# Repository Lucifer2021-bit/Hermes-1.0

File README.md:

# Hermes-1.0
PCB para aplicación de comedor para mascotas

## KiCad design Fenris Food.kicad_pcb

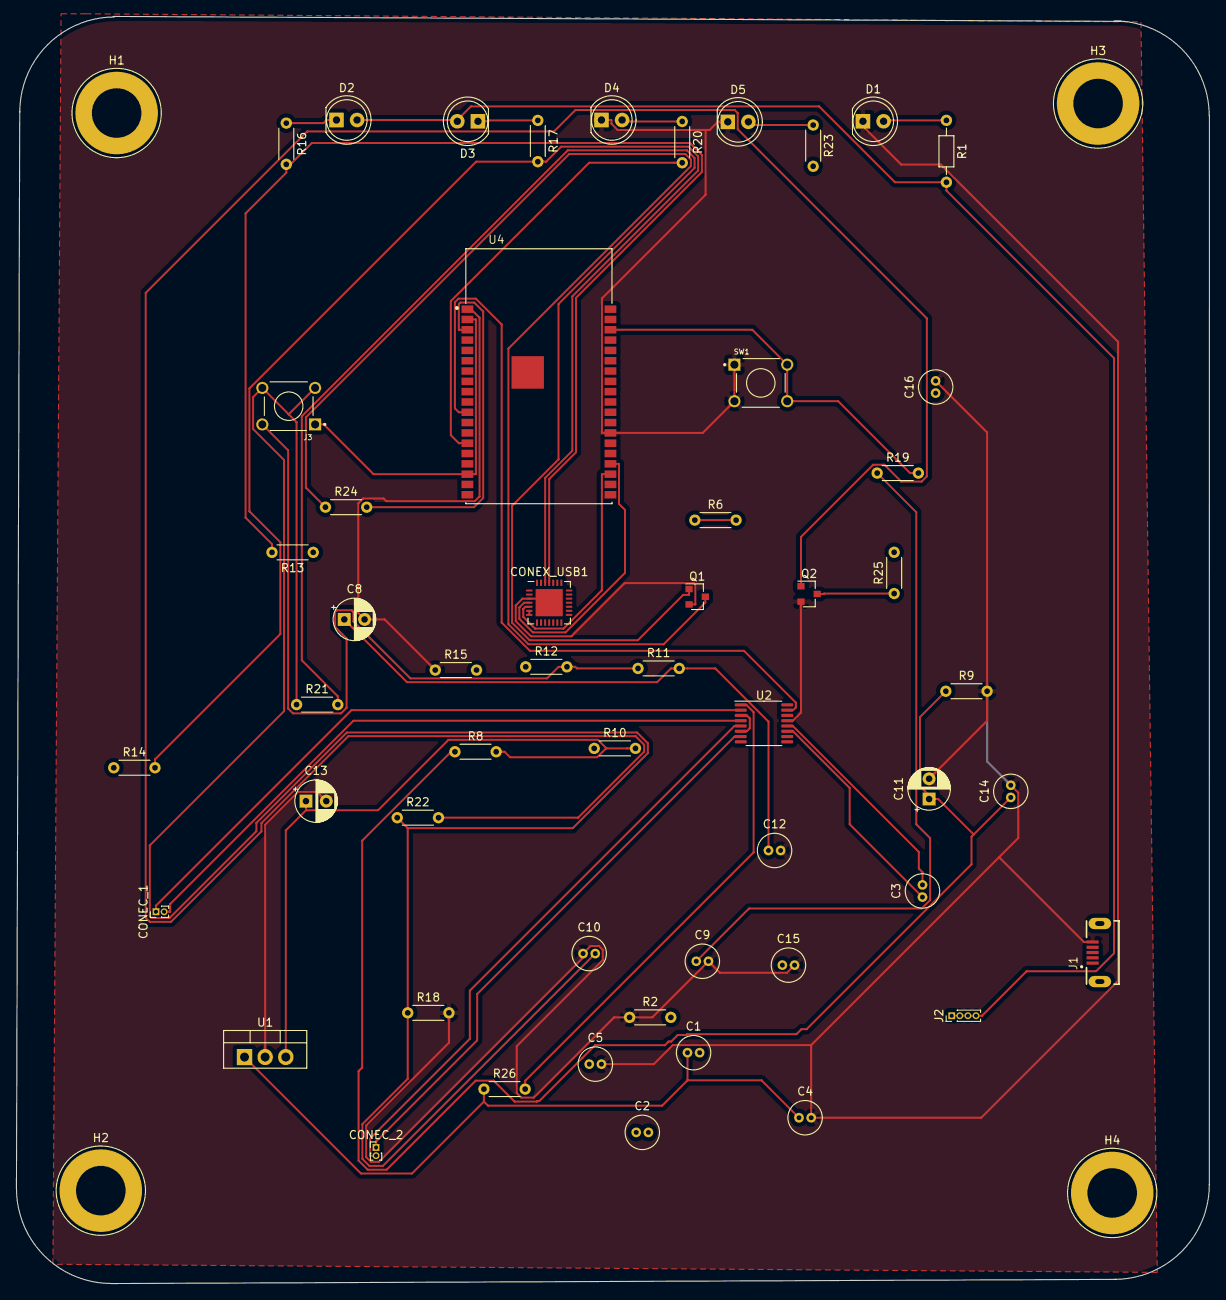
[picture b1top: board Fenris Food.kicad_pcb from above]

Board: 2 copper layers, 146.9 x 156.0 mm, 57 parts (0 on the bottom side), 38 nets.

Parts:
C1: 0.33uF; C_Radial_D4.0mm_H5.0mm_P1.50mm
C2, C9, C10, C12, C14, C16: 0.1uF; C_Radial_D4.0mm_H5.0mm_P1.50mm
C3: 0.01uF; C_Radial_D4.0mm_H5.0mm_P1.50mm
C4: 10uF?; C_Radial_D4.0mm_H5.0mm_P1.50mm
C5: 2.2uF; C_Radial_D4.0mm_H5.0mm_P1.50mm
C8, C11: 10uF; CP_Radial_D5.0mm_P2.50mm
C13: 100uF; CP_Radial_D5.0mm_P2.50mm
C15: 1uF; C_Radial_D4.0mm_H5.0mm_P1.50mm
CONEC_1, CONEC_2: Screw_Terminal_01x02; PinHeader_1x02_P1.00mm_Vertical
CONEX_USB1: CP2102N-A01-GQFN28; QFN-28-1EP_5x5mm_P0.5mm_EP3.35x3.35mm
D1, D2, D3, D4, D5: LED; LED_D5.0mm
H1, H2, H3, H4: MountingHole; Banana_Jack_1Pin
J1: USB_B_Micro; GCT_USB3140-30-0230-1-C_REVE1
J2: Screw_Terminal_01x04; PinHeader_1x04_P1.00mm_Vertical
J3: Conn_02x02_Top_Bottom; PULSEBUTTON
Q1, Q2: BSS138; SOT-23
R1: 330; R_Axial_DIN0204_L3.6mm_D1.6mm_P7.62mm_Horizontal
R2: 200m; R_Axial_DIN0204_L3.6mm_D1.6mm_P5.08mm_Horizontal
R6, R10, R18: 10K; R_Axial_DIN0204_L3.6mm_D1.6mm_P5.08mm_Horizontal
R8: 22.1K; R_Axial_DIN0204_L3.6mm_D1.6mm_P5.08mm_Horizontal
R9: 47.5K; R_Axial_DIN0204_L3.6mm_D1.6mm_P5.08mm_Horizontal
R11: 5; R_Axial_DIN0204_L3.6mm_D1.6mm_P5.08mm_Horizontal
R12, R16, R17: 2K; R_Axial_DIN0204_L3.6mm_D1.6mm_P5.08mm_Horizontal
R13, R14, R15: 10k; R_Axial_DIN0204_L3.6mm_D1.6mm_P5.08mm_Horizontal
R19, R21, R22: 1K; R_Axial_DIN0204_L3.6mm_D1.6mm_P5.08mm_Horizontal
R20, R23: 330; R_Axial_DIN0204_L3.6mm_D1.6mm_P5.08mm_Horizontal
R24, R25: R; R_Axial_DIN0204_L3.6mm_D1.6mm_P5.08mm_Horizontal
R26: 47K; R_Axial_DIN0204_L3.6mm_D1.6mm_P5.08mm_Horizontal
SW1: SW_Push_LED; PULSEBUTTON
U1: LM7812_TO220; TO-220-3_Vertical
U2: DRV8833PW; TSSOP-16_4.4x5mm_P0.65mm
U4: ESP32-S2-WROVER; ESP32-WROVER-B

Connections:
+3V3: C2.1, C13.1, C15.1, D2.2, D3.2, J2.1, J2.2, J2.3, J2.4, J3.1, J3.2, R1.2, R6.1, R6.2, R8.2, R10.2, R11.1, R12.2, U1.3, U4.2, U4.17
+5V: C1.1, C3.2, C4.1, R26.1, U1.1, U2.12
/Comunicacion/CONTROL: R20.2, U4.14
/Comunicacion/D+_USB: CONEX_USB1.4, J1.3, U4.23
/Comunicacion/D-_USB: CONEX_USB1.5, J1.2, U4.22
/Comunicacion/EN: C9.1, R10.1, R19.1
/Comunicacion/ESP_RST: C16.1, R19.2, SW1.2, SW1.4, U4.36
/Comunicacion/IN1: U2.9, U2.16, U4.10
/Comunicacion/IN2: U2.10, U2.15, U4.11
/Comunicacion/IO0: R24.2, U4.3
/Comunicacion/IO1: R25.2, U4.4
/Comunicacion/IO4: R23.2, U4.7
/Comunicacion/REGIN: C8.1, C12.1, CONEX_USB1.6, CONEX_USB1.7, R11.2
/Comunicacion/RXD: CONEX_USB1.25, R13.2, R16.2
/Comunicacion/TXD: CONEX_USB1.26, R14.2, R17.2
/Comunicacion/VBUS_TX: C11.1, C14.1, CONEX_USB1.8, R8.1, R9.1, U4.24
/VCC/MTR1: CONEC_1.1, U2.2
/VCC/MTR2: CONEC_1.2, U2.4
/VCC/MTR3: CONEC_2.1, U2.7
/VCC/MTR4: CONEC_2.2, U2.5
GND: C4.2, C5.2, C8.2, C9.2, C10.1, C11.2, C12.2, C13.2, C14.2, C15.2, C16.2, CONEX_USB1.3, CONEX_USB1.29, D1.1, D4.1, D5.1, J1.5, Q1.2, Q2.2, R2.1, R9.2, R15.1, R18.2, SW1.1, SW1.3, U1.2, U2.13, U4.1, U4.26
unnamed: C1.2, C2.2
unnamed: C3.1, U2.11
unnamed: C5.1, U2.14
unnamed: C10.2, J3.3, J3.4, R18.1, R21.1, R22.1
unnamed: CONEX_USB1.9, R12.1
unnamed: CONEX_USB1.11, R15.2
unnamed: D1.2, R1.1
unnamed: D2.1, R16.1
unnamed: D3.1, R17.1
unnamed: D4.2, R20.1
unnamed: D5.2, R23.1
unnamed: Q1.1, R21.2
unnamed: Q1.3, R24.1
unnamed: Q2.1, R22.2
unnamed: Q2.3, R25.1
unnamed: R2.2, U2.3, U2.6
unnamed: R26.2, U2.1
